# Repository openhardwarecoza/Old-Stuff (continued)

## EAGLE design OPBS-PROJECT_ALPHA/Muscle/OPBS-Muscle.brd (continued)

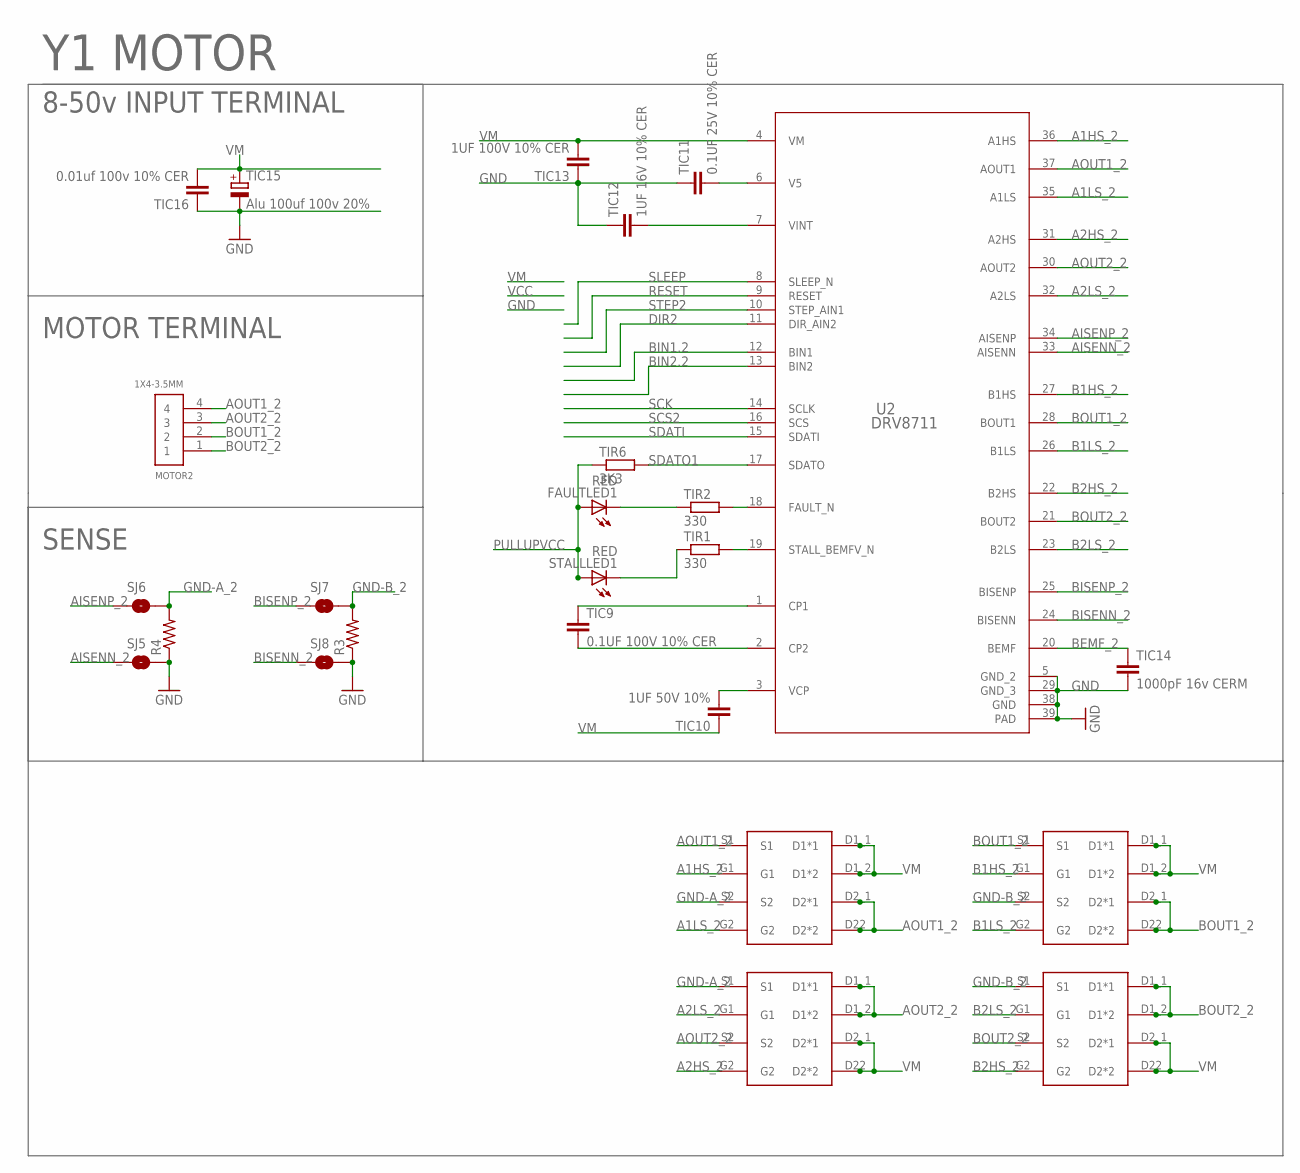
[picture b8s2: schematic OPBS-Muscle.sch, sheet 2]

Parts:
FAULTLED1: RED; 1206
MOTOR2: 1X4-3.5MM; 1X04-3.5MM
R3, R4: R-US_R2512; R2512
SJ5, SJ6, SJ7, SJ8: SOLDERJUMPERTRACE; SJ_2S-TRACE
STALLLED1: RED; 1206
TIC9: 0.1UF 100V 10% CER; C0603K
TIC10: 1UF 50V 10%; C0805K
TIC11: 0.1UF 25V 10% CER; C0603K
TIC12: 1UF 16V 10% CER; C0603K
TIC13: 1UF 100V 10% CER; C1206K
TIC14: 1000pF 16v CERM; C0603K
TIC15: Alu 100uf 100v 20%; E5-10,5
TIC16: 0.01uf 100v 10% CER; C0603K
TIR1, TIR2: 330; R1206
TIR6: 3K3; R1206
U2: DRV8711; DCP0038A_N
U$5, U$6, U$7, U$8: CSD88537ND

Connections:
A1HS_2: U2.36 (A1HS), U$5.G1
A1LS_2: U2.35 (A1LS), U$5.G2
A2HS_2: U2.31 (A2HS), U$7.G2
A2LS_2: U2.32 (A2LS), U$7.G1
AISENN_2: SJ5.1, U2.33 (AISENN)
AISENP_2: SJ6.1, U2.34 (AISENP)
AOUT1_2: MOTOR2.4, U2.37 (AOUT1), U$5.D2_1 (D2*1), U$5.D22 (D2*2), U$5.S1
AOUT2_2: MOTOR2.3, U2.30 (AOUT2), U$7.D1_1 (D1*1), U$7.D1_2 (D1*2), U$7.S2
B1HS_2: U2.27 (B1HS), U$6.G1
B1LS_2: U2.26 (B1LS), U$6.G2
B2HS_2: U2.22 (B2HS), U$8.G2
B2LS_2: U2.23 (B2LS), U$8.G1
BEMF_2: TIC14.1, U2.20 (BEMF)
BIN1.2: U2.12 (BIN1)
BIN2.2: U2.13 (BIN2)
BISENN_2: SJ8.1, U2.24 (BISENN)
BISENP_2: SJ7.1, U2.25 (BISENP)
BOUT1_2: MOTOR2.2, U2.28 (BOUT1), U$6.D2_1 (D2*1), U$6.D22 (D2*2), U$6.S1
BOUT2_2: MOTOR2.1, U2.21 (BOUT2), U$8.D1_1 (D1*1), U$8.D1_2 (D1*2), U$8.S2
CP1_2: TIC9.1, U2.1 (CP1)
CP2_2: TIC9.2, U2.2 (CP2)
DIR2: U2.11 (DIR_AIN2); also elsewhere on the board
FAULTLED2: FAULTLED1.C, TIR2.1
FAULT_N2: TIR2.2, U2.18 (FAULT_N)
GND: R3.1, R4.1, SJ5.2, SJ8.2, TIC11.1, TIC12.1, TIC13.1, TIC14.2, TIC15.-, TIC16.1, U2.5 (GND_2), U2.29 (GND_3), U2.38 (GND), U2.39 (PAD); also elsewhere on the board
GND-A_2: R4.2, SJ6.2, U$5.S2, U$7.S1
GND-B_2: R3.2, SJ7.2, U$6.S2, U$8.S1
PULLUPVCC: FAULTLED1.A, STALLLED1.A, TIR6.1; also elsewhere on the board
RESET: U2.9 (RESET); also elsewhere on the board
SCK: U2.14 (SCLK); also elsewhere on the board
SCS2: U2.16 (SCS); also elsewhere on the board
SDATI: U2.15 (SDATI); also elsewhere on the board
SDATO1: TIR6.2, U2.17 (SDATO); also elsewhere on the board
SLEEP: U2.8 (SLEEP_N); also elsewhere on the board
STALLLED2: STALLLED1.C, TIR1.1
STALL_N2: TIR1.2, U2.19 (STALL_BEMFV_N)
STEP2: U2.10 (STEP_AIN1); also elsewhere on the board
V5_2: TIC11.2, U2.6 (V5)
VCP2: TIC10.2, U2.3 (VCP)
VINT2: TIC12.2, U2.7 (VINT)
VM: TIC10.1, TIC13.2, TIC15.+, TIC16.2, U2.4 (VM), U$5.D1_1 (D1*1), U$5.D1_2 (D1*2), U$6.D1_1 (D1*1), U$6.D1_2 (D1*2), U$7.D2_1 (D2*1), U$7.D22 (D2*2), U$8.D2_1 (D2*1), U$8.D22 (D2*2); also elsewhere on the board

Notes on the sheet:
8-50v INPUT TERMINAL
MOTOR TERMINAL
SENSE
Y1 MOTOR

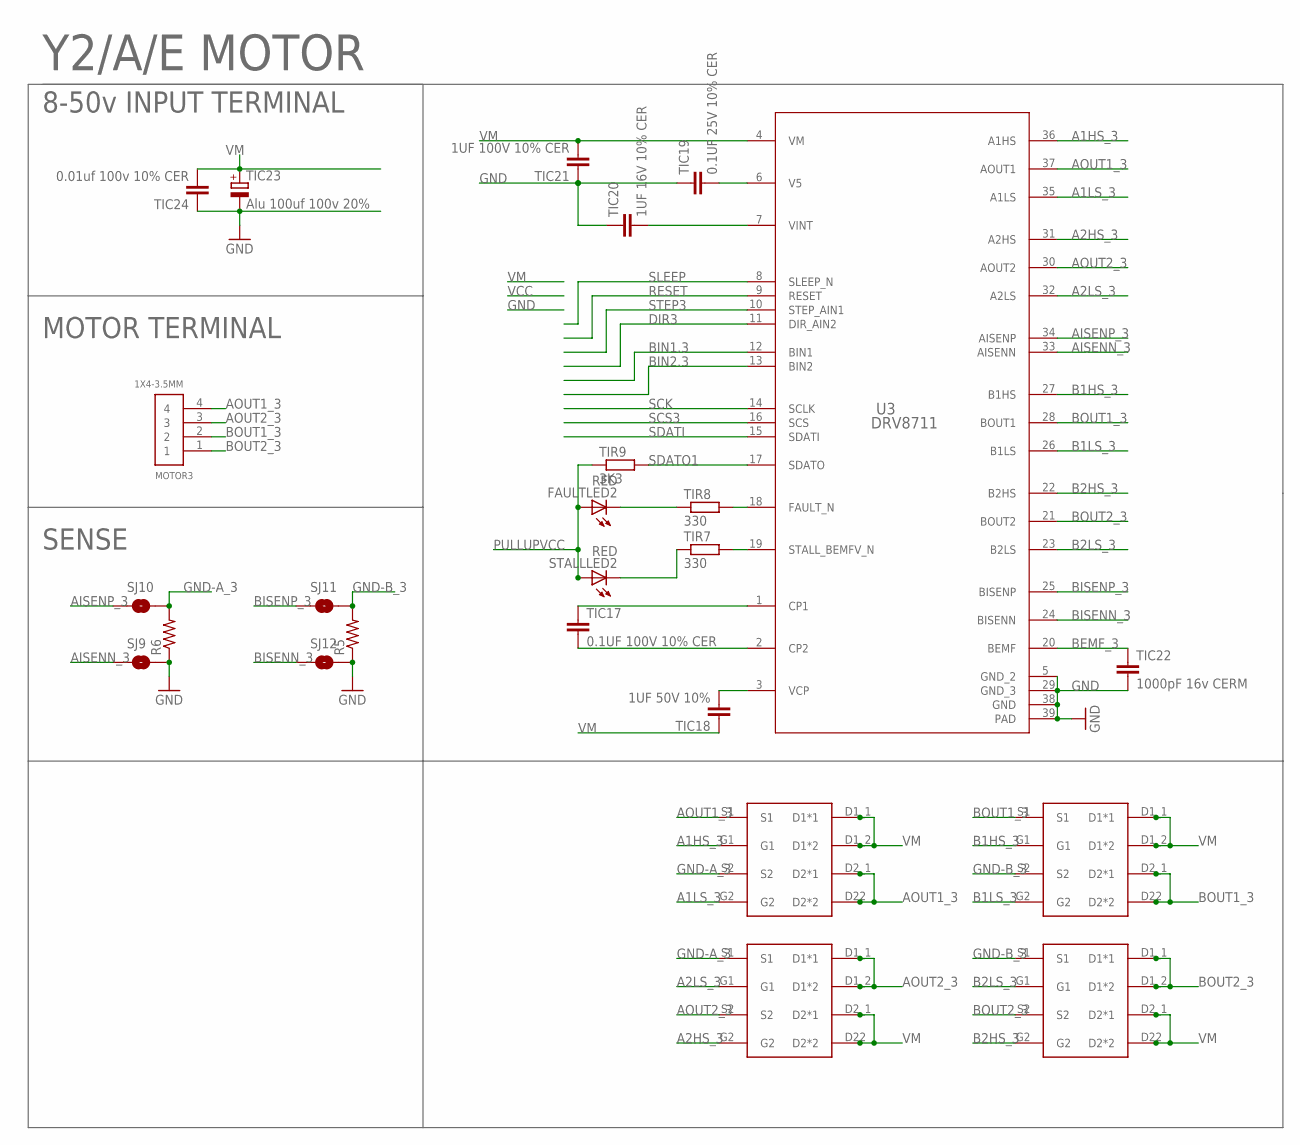
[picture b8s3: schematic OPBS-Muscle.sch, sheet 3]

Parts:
FAULTLED2: RED; 1206
MOTOR3: 1X4-3.5MM; 1X04-3.5MM
R5, R6: R-US_R2512; R2512
SJ9, SJ10, SJ11, SJ12: SOLDERJUMPERTRACE; SJ_2S-TRACE
STALLLED2: RED; 1206
TIC17: 0.1UF 100V 10% CER; C0603K
TIC18: 1UF 50V 10%; C0805K
TIC19: 0.1UF 25V 10% CER; C0603K
TIC20: 1UF 16V 10% CER; C0603K
TIC21: 1UF 100V 10% CER; C1206K
TIC22: 1000pF 16v CERM; C0603K
TIC23: Alu 100uf 100v 20%; E5-10,5
TIC24: 0.01uf 100v 10% CER; C0603K
TIR7, TIR8: 330; R1206
TIR9: 3K3; R1206
U3: DRV8711; DCP0038A_N
U$9, U$10, U$11, U$12: CSD88537ND

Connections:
A1HS_3: U3.36 (A1HS), U$9.G1
A1LS_3: U3.35 (A1LS), U$9.G2
A2HS_3: U3.31 (A2HS), U$11.G2
A2LS_3: U3.32 (A2LS), U$11.G1
AISENN_3: SJ9.1, U3.33 (AISENN)
AISENP_3: SJ10.1, U3.34 (AISENP)
AOUT1_3: MOTOR3.4, U3.37 (AOUT1), U$9.D2_1 (D2*1), U$9.D22 (D2*2), U$9.S1
AOUT2_3: MOTOR3.3, U3.30 (AOUT2), U$11.D1_1 (D1*1), U$11.D1_2 (D1*2), U$11.S2
B1HS_3: U3.27 (B1HS), U$10.G1
B1LS_3: U3.26 (B1LS), U$10.G2
B2HS_3: U3.22 (B2HS), U$12.G2
B2LS_3: U3.23 (B2LS), U$12.G1
BEMF_3: TIC22.1, U3.20 (BEMF)
BIN1.3: U3.12 (BIN1)
BIN2.3: U3.13 (BIN2)
BISENN_3: SJ12.1, U3.24 (BISENN)
BISENP_3: SJ11.1, U3.25 (BISENP)
BOUT1_3: MOTOR3.2, U3.28 (BOUT1), U$10.D2_1 (D2*1), U$10.D22 (D2*2), U$10.S1
BOUT2_3: MOTOR3.1, U3.21 (BOUT2), U$12.D1_1 (D1*1), U$12.D1_2 (D1*2), U$12.S2
CP1_3: TIC17.1, U3.1 (CP1)
CP2_3: TIC17.2, U3.2 (CP2)
DIR3: U3.11 (DIR_AIN2); also elsewhere on the board
FAULTLED3: FAULTLED2.C, TIR8.1
FAULT_N3: TIR8.2, U3.18 (FAULT_N)
GND: R5.1, R6.1, SJ9.2, SJ12.2, TIC19.1, TIC20.1, TIC21.1, TIC22.2, TIC23.-, TIC24.1, U3.5 (GND_2), U3.29 (GND_3), U3.38 (GND), U3.39 (PAD); also elsewhere on the board
GND-A_3: R6.2, SJ10.2, U$9.S2, U$11.S1
GND-B_3: R5.2, SJ11.2, U$10.S2, U$12.S1
PULLUPVCC: FAULTLED2.A, STALLLED2.A, TIR9.1; also elsewhere on the board
RESET: U3.9 (RESET); also elsewhere on the board
SCK: U3.14 (SCLK); also elsewhere on the board
SCS3: U3.16 (SCS); also elsewhere on the board
SDATI: U3.15 (SDATI); also elsewhere on the board
SDATO1: TIR9.2, U3.17 (SDATO); also elsewhere on the board
SLEEP: U3.8 (SLEEP_N); also elsewhere on the board
STALLLED3: STALLLED2.C, TIR7.1
STALL_N3: TIR7.2, U3.19 (STALL_BEMFV_N)
STEP3: U3.10 (STEP_AIN1); also elsewhere on the board
V5_3: TIC19.2, U3.6 (V5)
VCP3: TIC18.2, U3.3 (VCP)
VINT3: TIC20.2, U3.7 (VINT)
VM: TIC18.1, TIC21.2, TIC23.+, TIC24.2, U3.4 (VM), U$9.D1_1 (D1*1), U$9.D1_2 (D1*2), U$10.D1_1 (D1*1), U$10.D1_2 (D1*2), U$11.D2_1 (D2*1), U$11.D22 (D2*2), U$12.D2_1 (D2*1), U$12.D22 (D2*2); also elsewhere on the board

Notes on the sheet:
8-50v INPUT TERMINAL
MOTOR TERMINAL
SENSE
Y2/A/E MOTOR

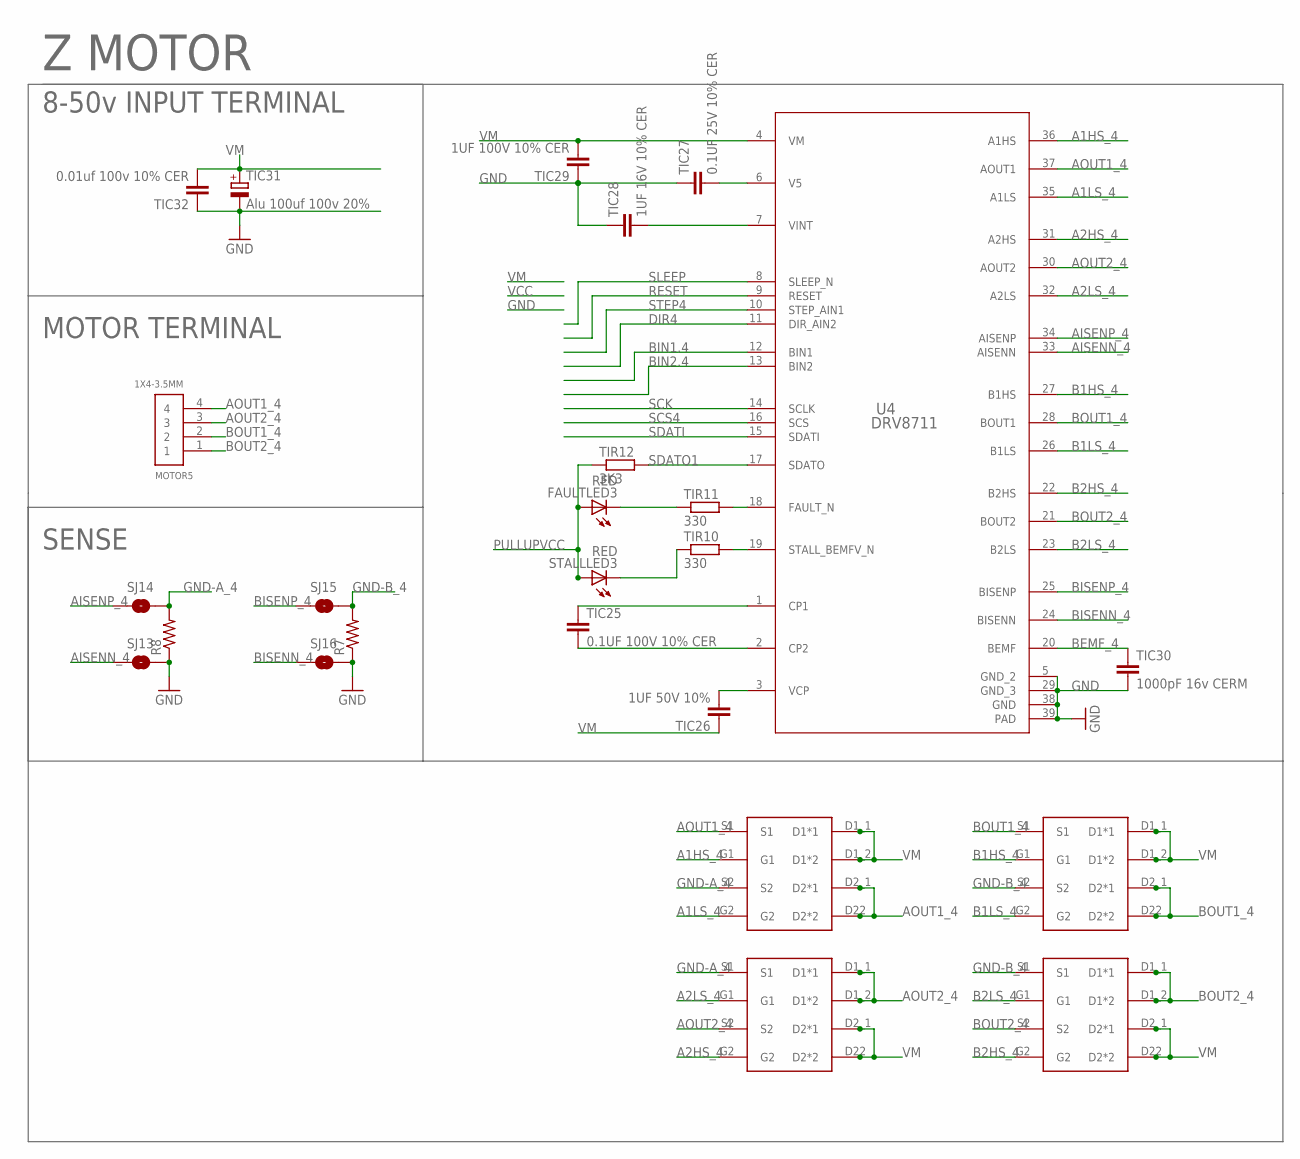
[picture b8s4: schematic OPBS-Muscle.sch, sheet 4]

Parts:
FAULTLED3: RED; 1206
MOTOR5: 1X4-3.5MM; 1X04-3.5MM
R7, R8: R-US_R2512; R2512
SJ13, SJ14, SJ15, SJ16: SOLDERJUMPERTRACE; SJ_2S-TRACE
STALLLED3: RED; 1206
TIC25: 0.1UF 100V 10% CER; C0603K
TIC26: 1UF 50V 10%; C0805K
TIC27: 0.1UF 25V 10% CER; C0603K
TIC28: 1UF 16V 10% CER; C0603K
TIC29: 1UF 100V 10% CER; C1206K
TIC30: 1000pF 16v CERM; C0603K
TIC31: Alu 100uf 100v 20%; E5-10,5
TIC32: 0.01uf 100v 10% CER; C0603K
TIR10, TIR11: 330; R1206
TIR12: 3K3; R1206
U4: DRV8711; DCP0038A_N
U$13, U$14, U$15, U$16: CSD88537ND

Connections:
A1HS_4: U4.36 (A1HS), U$13.G1
A1LS_4: U4.35 (A1LS), U$13.G2
A2HS_4: U4.31 (A2HS), U$15.G2
A2LS_4: U4.32 (A2LS), U$15.G1
AISENN_4: SJ13.1, U4.33 (AISENN)
AISENP_4: SJ14.1, U4.34 (AISENP)
AOUT1_4: MOTOR5.4, U4.37 (AOUT1), U$13.D2_1 (D2*1), U$13.D22 (D2*2), U$13.S1
AOUT2_4: MOTOR5.3, U4.30 (AOUT2), U$15.D1_1 (D1*1), U$15.D1_2 (D1*2), U$15.S2
B1HS_4: U4.27 (B1HS), U$14.G1
B1LS_4: U4.26 (B1LS), U$14.G2
B2HS_4: U4.22 (B2HS), U$16.G2
B2LS_4: U4.23 (B2LS), U$16.G1
BEMF_4: TIC30.1, U4.20 (BEMF)
BIN1.4: U4.12 (BIN1)
BIN2.4: U4.13 (BIN2)
BISENN_4: SJ16.1, U4.24 (BISENN)
BISENP_4: SJ15.1, U4.25 (BISENP)
BOUT1_4: MOTOR5.2, U4.28 (BOUT1), U$14.D2_1 (D2*1), U$14.D22 (D2*2), U$14.S1
BOUT2_4: MOTOR5.1, U4.21 (BOUT2), U$16.D1_1 (D1*1), U$16.D1_2 (D1*2), U$16.S2
CP1_4: TIC25.1, U4.1 (CP1)
CP2_4: TIC25.2, U4.2 (CP2)
DIR4: U4.11 (DIR_AIN2); also elsewhere on the board
FAULTLED4: FAULTLED3.C, TIR11.1
FAULT_N4: TIR11.2, U4.18 (FAULT_N)
GND: R7.1, R8.1, SJ13.2, SJ16.2, TIC27.1, TIC28.1, TIC29.1, TIC30.2, TIC31.-, TIC32.1, U4.5 (GND_2), U4.29 (GND_3), U4.38 (GND), U4.39 (PAD); also elsewhere on the board
GND-A_4: R8.2, SJ14.2, U$13.S2, U$15.S1
GND-B_4: R7.2, SJ15.2, U$14.S2, U$16.S1
PULLUPVCC: FAULTLED3.A, STALLLED3.A, TIR12.1; also elsewhere on the board
RESET: U4.9 (RESET); also elsewhere on the board
SCK: U4.14 (SCLK); also elsewhere on the board
SCS4: U4.16 (SCS); also elsewhere on the board
SDATI: U4.15 (SDATI); also elsewhere on the board
SDATO1: TIR12.2, U4.17 (SDATO); also elsewhere on the board
SLEEP: U4.8 (SLEEP_N); also elsewhere on the board
STALLLED4: STALLLED3.C, TIR10.1
STALL_N4: TIR10.2, U4.19 (STALL_BEMFV_N)
STEP4: U4.10 (STEP_AIN1); also elsewhere on the board
V5_4: TIC27.2, U4.6 (V5)
VCP4: TIC26.2, U4.3 (VCP)
VINT4: TIC28.2, U4.7 (VINT)
VM: TIC26.1, TIC29.2, TIC31.+, TIC32.2, U4.4 (VM), U$13.D1_1 (D1*1), U$13.D1_2 (D1*2), U$14.D1_1 (D1*1), U$14.D1_2 (D1*2), U$15.D2_1 (D2*1), U$15.D22 (D2*2), U$16.D2_1 (D2*1), U$16.D22 (D2*2); also elsewhere on the board

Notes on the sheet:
8-50v INPUT TERMINAL
MOTOR TERMINAL
SENSE
Z MOTOR

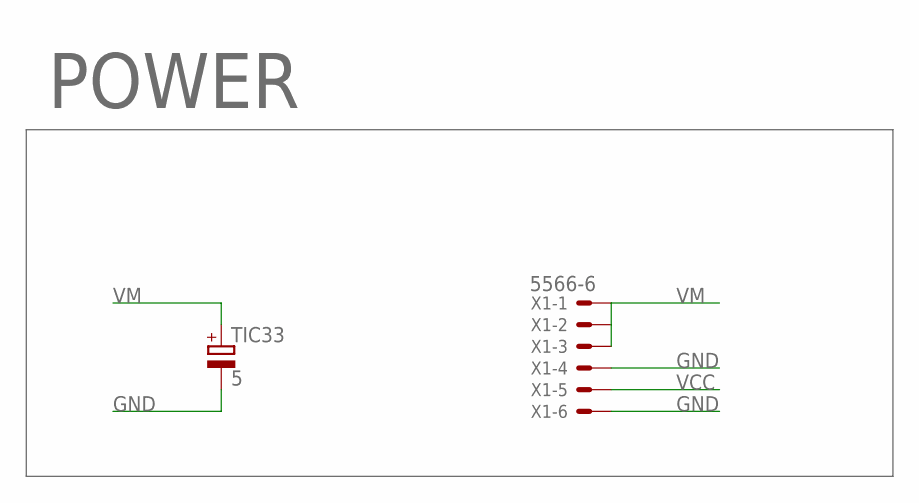
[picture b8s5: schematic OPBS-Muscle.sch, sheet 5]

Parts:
TIC33: 5; E5-10,5
X1: 5566-6

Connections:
GND: TIC33.-, X1.4, X1.6; also elsewhere on the board
VCC: X1.5; also elsewhere on the board
VM: TIC33.+, X1.1, X1.2, X1.3; also elsewhere on the board

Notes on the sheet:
POWER

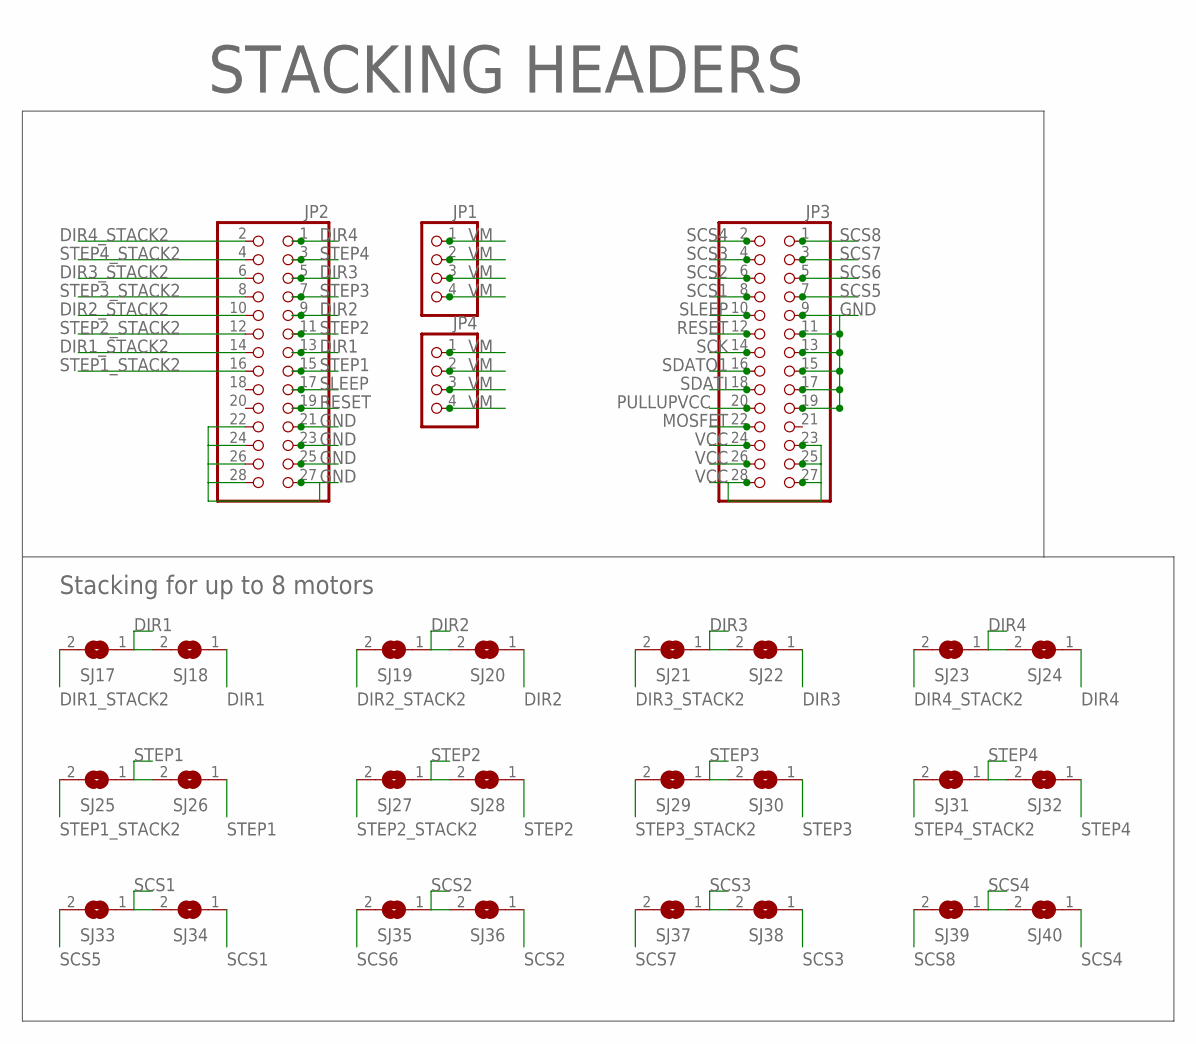
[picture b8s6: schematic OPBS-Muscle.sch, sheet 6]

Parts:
JP1, JP4: PINHD-1X4; 1X04
JP2, JP3: PINHD-2X14; 2X14
SJ17, SJ18, SJ19, SJ20, SJ21, SJ22, SJ23, SJ24, SJ25, SJ26, SJ27, SJ28, SJ29, SJ30, SJ31, SJ32, SJ33, SJ34, SJ35, SJ36, SJ37, SJ38, SJ39, SJ40: SJ

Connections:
DIR1: JP2.13, SJ17.1, SJ18.1, SJ18.2; also elsewhere on the board
DIR1_STACK2: JP2.14, SJ17.2
DIR2: JP2.9, SJ19.1, SJ20.1, SJ20.2; also elsewhere on the board
DIR2_STACK2: JP2.10, SJ19.2
DIR3: JP2.5, SJ21.1, SJ22.1, SJ22.2; also elsewhere on the board
DIR3_STACK2: JP2.6, SJ21.2
DIR4: JP2.1, SJ23.1, SJ24.1, SJ24.2; also elsewhere on the board
DIR4_STACK2: JP2.2, SJ23.2
GND: JP2.21, JP2.22, JP2.23, JP2.24, JP2.25, JP2.26, JP2.27, JP2.28, JP3.9, JP3.11, JP3.13, JP3.15, JP3.17, JP3.19; also elsewhere on the board
MOSFET: JP3.22; also elsewhere on the board
PULLUPVCC: JP3.20; also elsewhere on the board
RESET: JP2.19, JP3.12; also elsewhere on the board
SCK: JP3.14; also elsewhere on the board
SCS1: JP3.8, SJ33.1, SJ34.1, SJ34.2; also elsewhere on the board
SCS2: JP3.6, SJ35.1, SJ36.1, SJ36.2; also elsewhere on the board
SCS3: JP3.4, SJ37.1, SJ38.1, SJ38.2; also elsewhere on the board
SCS4: JP3.2, SJ39.1, SJ40.1, SJ40.2; also elsewhere on the board
SCS5: JP3.7, SJ33.2
SCS6: JP3.5, SJ35.2
SCS7: JP3.3, SJ37.2
SCS8: JP3.1, SJ39.2
SDATI: JP3.18; also elsewhere on the board
SDATO1: JP3.16; also elsewhere on the board
SLEEP: JP2.17, JP3.10; also elsewhere on the board
STEP1: JP2.15, SJ25.1, SJ26.1, SJ26.2; also elsewhere on the board
STEP1_STACK2: JP2.16, SJ25.2
STEP2: JP2.11, SJ27.1, SJ28.1, SJ28.2; also elsewhere on the board
STEP2_STACK2: JP2.12, SJ27.2
STEP3: JP2.7, SJ29.1, SJ30.1, SJ30.2; also elsewhere on the board
STEP3_STACK2: JP2.8, SJ29.2
STEP4: JP2.3, SJ31.1, SJ32.1, SJ32.2; also elsewhere on the board
STEP4_STACK2: JP2.4, SJ31.2
VCC: JP3.23, JP3.24, JP3.25, JP3.26, JP3.27, JP3.28; also elsewhere on the board
VM: JP1.1, JP1.2, JP1.3, JP1.4, JP4.1, JP4.2, JP4.3, JP4.4; also elsewhere on the board

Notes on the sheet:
STACKING HEADERS
Stacking for up to 8 motors

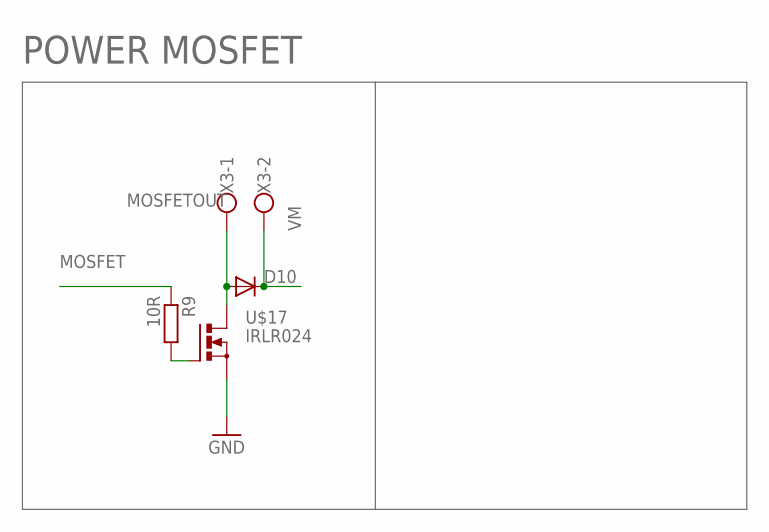
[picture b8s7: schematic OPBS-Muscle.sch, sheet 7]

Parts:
D10: DIODESMA-ALT; SMA-DIODE_ALT
R9: 10R; M1206
U$17: IRLR024; D-PAK_TO252AA
X3: W237-102

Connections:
GND: U$17.3 (SOURCE); also elsewhere on the board
MOSFET: R9.1; also elsewhere on the board
MOSFETOUT: D10.A, U$17.2 (DRAIN), X3.1
unnamed: R9.2, U$17.1 (GATE)
VM: D10.C, X3.2; also elsewhere on the board

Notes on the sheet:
POWER MOSFET

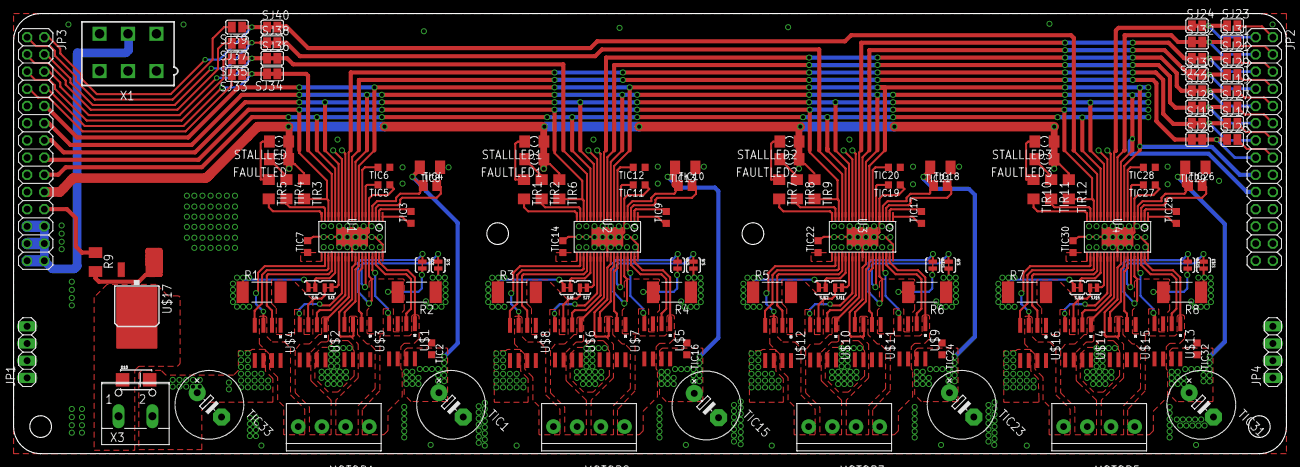
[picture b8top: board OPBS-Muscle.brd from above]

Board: 2 copper layers, 188.0 x 65.0 mm, 134 parts (0 on the bottom side), 148 nets.

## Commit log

2018-10-23 Archive
2019-03-07 elcheapo
